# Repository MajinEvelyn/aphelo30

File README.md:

# aphelo30

Pictured with Chicago Steno keycaps by [Asymplex](https://www.asymplex.xyz/), case printed in Cream PETG-HF.

## Design Parameters
- Full split
- ZMK powered BLE wireless
- Nice! Nano v2 controlled
- Reversible PCB
- 30 keys in 3x5 configuration
- Choc v1 Switches with hotswap sockets
- No thumb keys
- Aggressive splay

Named for the *Aphelocoma* genus of scrub jay birds. 

## Overview

This weird combination of features is designed for my hands, which no currently existing boards accommodate. I have RSI issues in both of my thumbs, to the point that even single thumb key layouts don't work for me. Aside from this, the aggressive splay and finger positions were made with Ergopad, and recreated in Ergogen. 

In this repo you will find all files related to the design process, including the Ergogen config, KiCAD PCB files, related Gerbers, and case 3d files for printing. Unfortunately, I was only able to get the PCB to a 115x85mm footprint with this splay, so a little outside of the <100x100mm discount size for JLCPCB. Despite this and the expensive microcontroller, you should be able to build this board for somewhere between 80-120$.

## Case

There are 4 bosses for heat set inserts on the underside of each half's top case. Press them into each boss with a soldering iron, and use your M2 screws through the holes in the bottom case to screw into the heat set inserts.
There are heat set insert soldering tips available for pretty cheap to make this process easy, but I've heard this is easy enough with typical soldering iron tips.

## Carrying Case

I designed this to slide in both halves vertically, with the USB ports facing up and open air to protect the keycaps. It is not fully enclosed because for my use case I am placing it in a bag. I glued some felt to the bottom of the case to cushion it, and ribbons to make pulling the keeb halves out easy.

## Firmware
ZMK: https://github.com/MajinEvelyn/zmk-config-aphelo30

## BOM

| Name | Count | Notes |
| ---- | ----- | ---------- |
| PCB | 2 | These are reversible, so either PCB works with either half. |
| Nice! Nano v2 MCU | 2 | |
| Choc v1 Switches | 30 | |
| Choc v1 Hotswap Sockets | 30 | |
| Choc v1 Keycaps | 30 | |
| Power Switch | 2 | |
| Reset Switch | 2 | You can omit these if you are fine with using ZMK reset behavior or shorting RST pins to reflash firmware. |
| 110mah LiPo Battery | 2 | There is plenty of space for other batteries inside the case, but I have not tested others. |
| Bumpons | 8 | Size is up to your preference. |
| M2(x8mm) Screws | 8 | Countersunk screws are best, they will seat perfectly into the chamfered holes in the bottom case. |
| M2 Heat Set Inserts | 8 | |

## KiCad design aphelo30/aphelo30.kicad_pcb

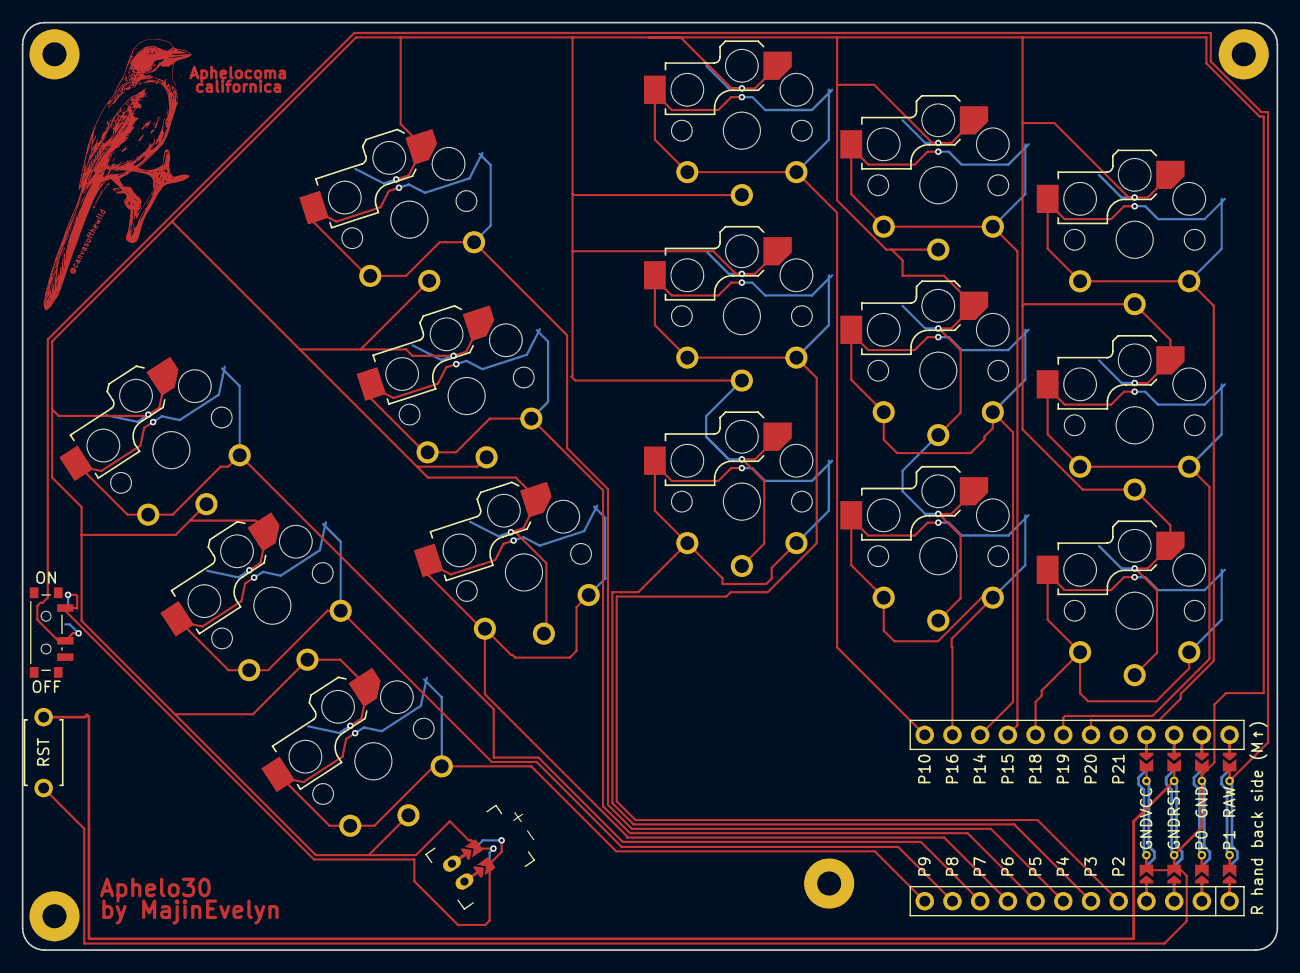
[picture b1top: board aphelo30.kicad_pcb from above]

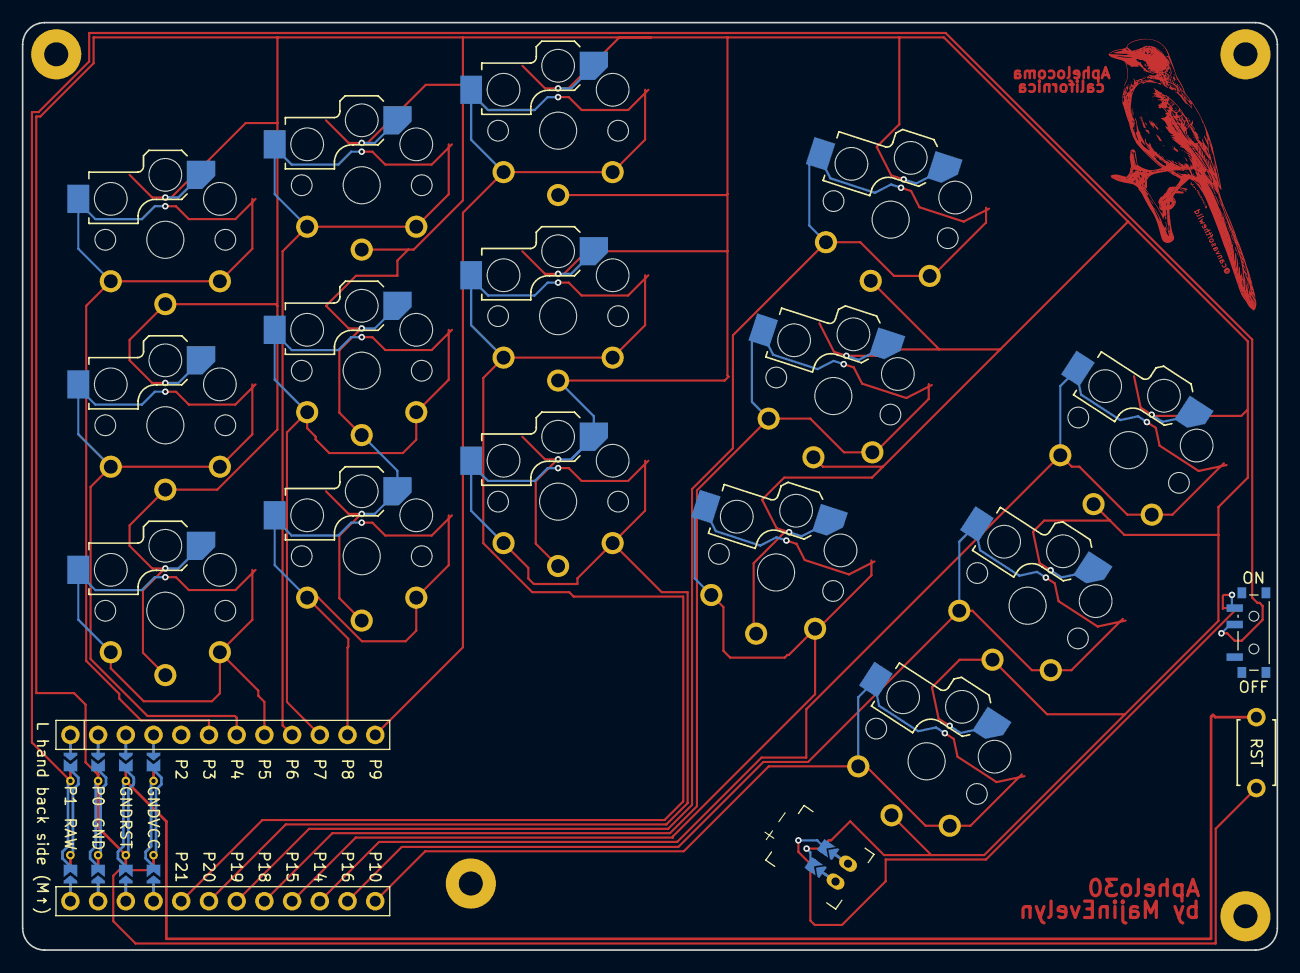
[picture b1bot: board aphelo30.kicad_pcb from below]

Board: 2 copper layers, 115.0 x 85.0 mm, 23 parts (15 on the bottom side), 21 nets.

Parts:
JST1: battery_connector_jst_ph_2
MCU1: mcu_nice_nano
MH1, MH2, MH3, MH4: mounting_hole_npth
PWR1: power_switch_smd_side
RST1: reset_switch_tht_top
S1, S2, S3, S4, S5, S6, S7, S8, S9, S10, S11, S12, S13, S14, S15: switch_choc_v1_v2

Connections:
BAT_P: JST1.1, PWR1.1, PWR1.3
GND: JST1.2, MCU1.103, MCU1.104, MCU1.123, RST1.2, S1.1, S1.2, S2.1, S2.2, S3.1, S3.2, S4.1, S4.2, S5.1, S5.2, S6.1, S6.2, S7.1, S7.2, S8.1, S8.2, S9.1, S9.2, S10.1, S10.2, S11.1, S11.2, S12.1, S12.2, S13.1, S13.2, S14.1, S14.2, S15.1, S15.2
JST1_1: JST1.11, JST1.21, JST1.31
JST1_2: JST1.12, JST1.22, JST1.32
P2: MCU1.5, S8.1, S8.2
P3: MCU1.6, S7.1, S7.2
P4: MCU1.7, S6.1, S6.2
P5: MCU1.8, S5.1, S5.2
P6: MCU1.9, S4.1, S4.2
P7: MCU1.10, S3.1, S3.2
P8: MCU1.11, S2.1, S2.2
P9: MCU1.12, S1.1, S1.2
P10: MCU1.13, S9.1, S9.2
P14: MCU1.15, S11.1, S11.2
P15: MCU1.16, S12.1, S12.2
P16: MCU1.14, S10.1, S10.2
P18: MCU1.17, S13.1, S13.2
P19: MCU1.18, S14.1, S14.2
P20: MCU1.19, S15.1, S15.2
RAW: MCU1.124, PWR1.2
RST: MCU1.122, RST1.1

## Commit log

2026-01-04 Rename aphelo30.step to aphelo30/aphelo30.step
2026-01-04 Rename aphelo30.stl to aphelo30/aphelo30.stl
2026-01-04 Rename california scrub jay.jpg to img/california scrub jay.jpg
2026-01-04 Rename ergopad left.png to img/ergopad left.png
2026-01-04 Rename ergopad righ.png to img/ergopad righ.png
2026-01-04 Update image format from PNG to JPG
2026-01-04 Fix image filename for scrub jay in README
2026-01-04 Fix image filename in README.md
2026-02-03 Rename image-10.jpg to scrub jay.jpg
2026-02-03 Fix image URL for scrub jay in README
2026-02-03 Rename Aphelo30 case bottom 1.5.3mf to case/Aphelo30 case bottom 1.5.3mf
2026-02-03 Enhance BOM section with additional notes
    Added additional notes for PCB, Reset Switch, LiPo Battery, Bumpons, and M2 Screws in the BOM section.
2026-02-04 Update README with keycaps and case information
    Added details about keycaps and case material.
2026-02-04 Add Apache License 2.0 to the project
